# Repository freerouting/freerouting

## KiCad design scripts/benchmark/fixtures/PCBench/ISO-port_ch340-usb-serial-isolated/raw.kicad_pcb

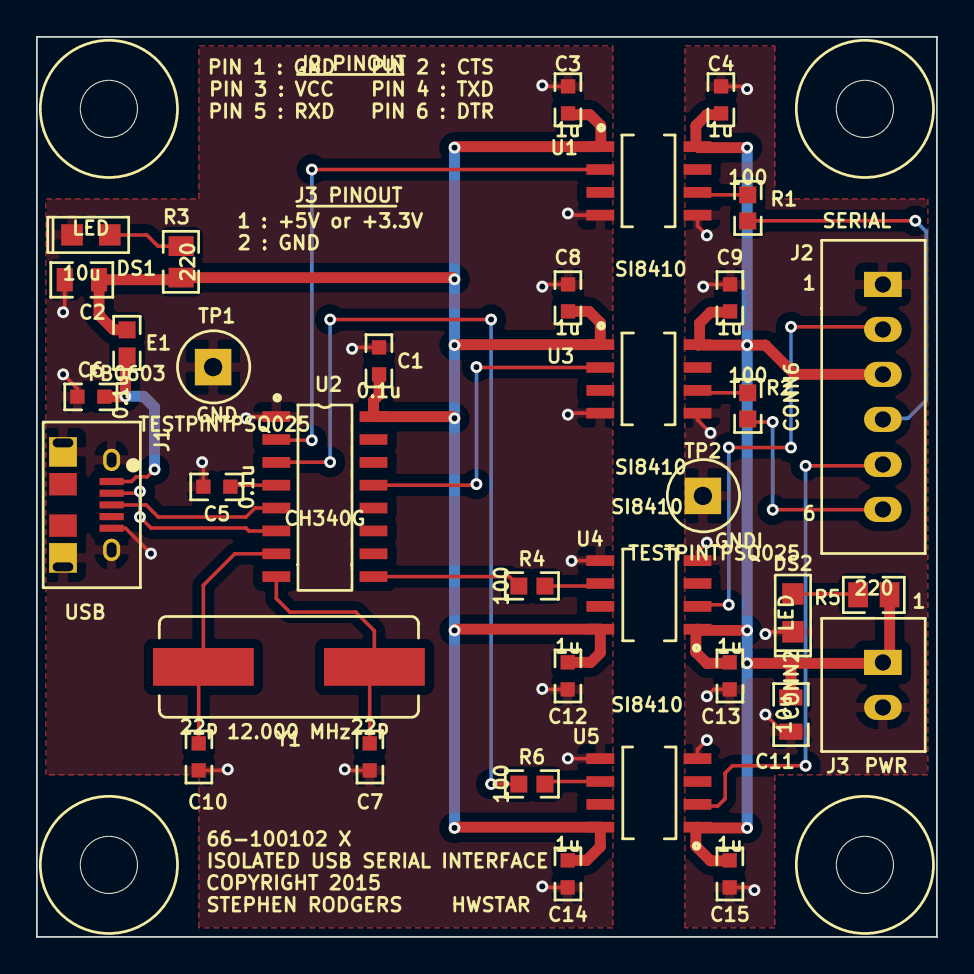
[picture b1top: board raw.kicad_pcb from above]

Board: 2 copper layers, 50.0 x 50.0 mm, 39 parts (0 on the bottom side), 24 nets.

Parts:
C1, C5, C6: 0.1u; CC0603
C2, C11: 10u; CC0805
C3, C4, C8, C9, C12, C13, C14, C15: 1u; CC0603
C7, C10: 22p; CC0603
DS1, DS2: LED; LED0805
E1: FB0603; RC0603
J1: CONN-USB-B-MICRO-FCI-11018194
J2: CONN6; JST_B6B_XH_A
J3: CONN2; JST_B2B_XH_A
MTG-HOLE-125-RING-300, MTG-HOLE-125-RING-300#2, MTG-HOLE-125-RING-300#3, MTG-HOLE-125-RING-300#4: VAL**; MTG-HOLE-125-RING-300
R1, R2, R4, R6: 100; RC0603
R3, R5: 220; RC0805
TP1, TP2: TESTPINTPSQ025; TESTPIN
U1, U3, U4, U5: SI8410; SOIC8N-SI8410
U2: CH340G; SOIC16N-SAR
Y1: 12.000 MHz; HC49US-SAR

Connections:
+5V: C1.1, C2.1, C3.1, C8.1, C12.1, C14.1, E1.2, R3.1, U1.1, U2.16, U3.1, U4.8, U5.8
+5VI: C4.1, C9.1, C11.1, C13.1, C15.1, J2.3, J3.1, R5.1, U1.8, U3.8, U4.1, U5.1
/CTSI: J2.2, U4.2
/CTSU: R4.1, U2.9
/D+: J1.3, U2.5
/D-: J1.2, U2.6
/DTRI: J2.6, R2.2
/DTRU: U2.13, U3.2
/RXDI: J2.5, U5.2
/RXDU: R6.1, U2.3
/TXDI: J2.4, R1.2
/TXDU: U1.2, U2.2
/VBUS: C6.1, E1.1, J1.1
GND: C1.2, C2.2, C3.2, C5.2, C6.2, C7.2, C8.2, C10.2, C12.2, C14.2, DS1.2, J1.5, J1.6, J1.7, J1.8, J1.9, TP1.1, U1.4, U2.1, U3.4, U4.5, U5.5
GNDI: C4.2, C9.2, C11.2, C13.2, C15.2, DS2.2, J2.1, J3.2, TP2.1, U1.5, U3.5, U4.4, U5.4
unnamed: R1.1, U1.6
unnamed: R6.2, U5.6
unnamed: DS2.1, R5.2
unnamed: DS1.1, R3.2
unnamed: R2.1, U3.6
unnamed: R4.2, U4.6
unnamed: C10.1, U2.7, Y1.1
unnamed: C5.1, U2.4
unnamed: C7.1, U2.8, Y1.2

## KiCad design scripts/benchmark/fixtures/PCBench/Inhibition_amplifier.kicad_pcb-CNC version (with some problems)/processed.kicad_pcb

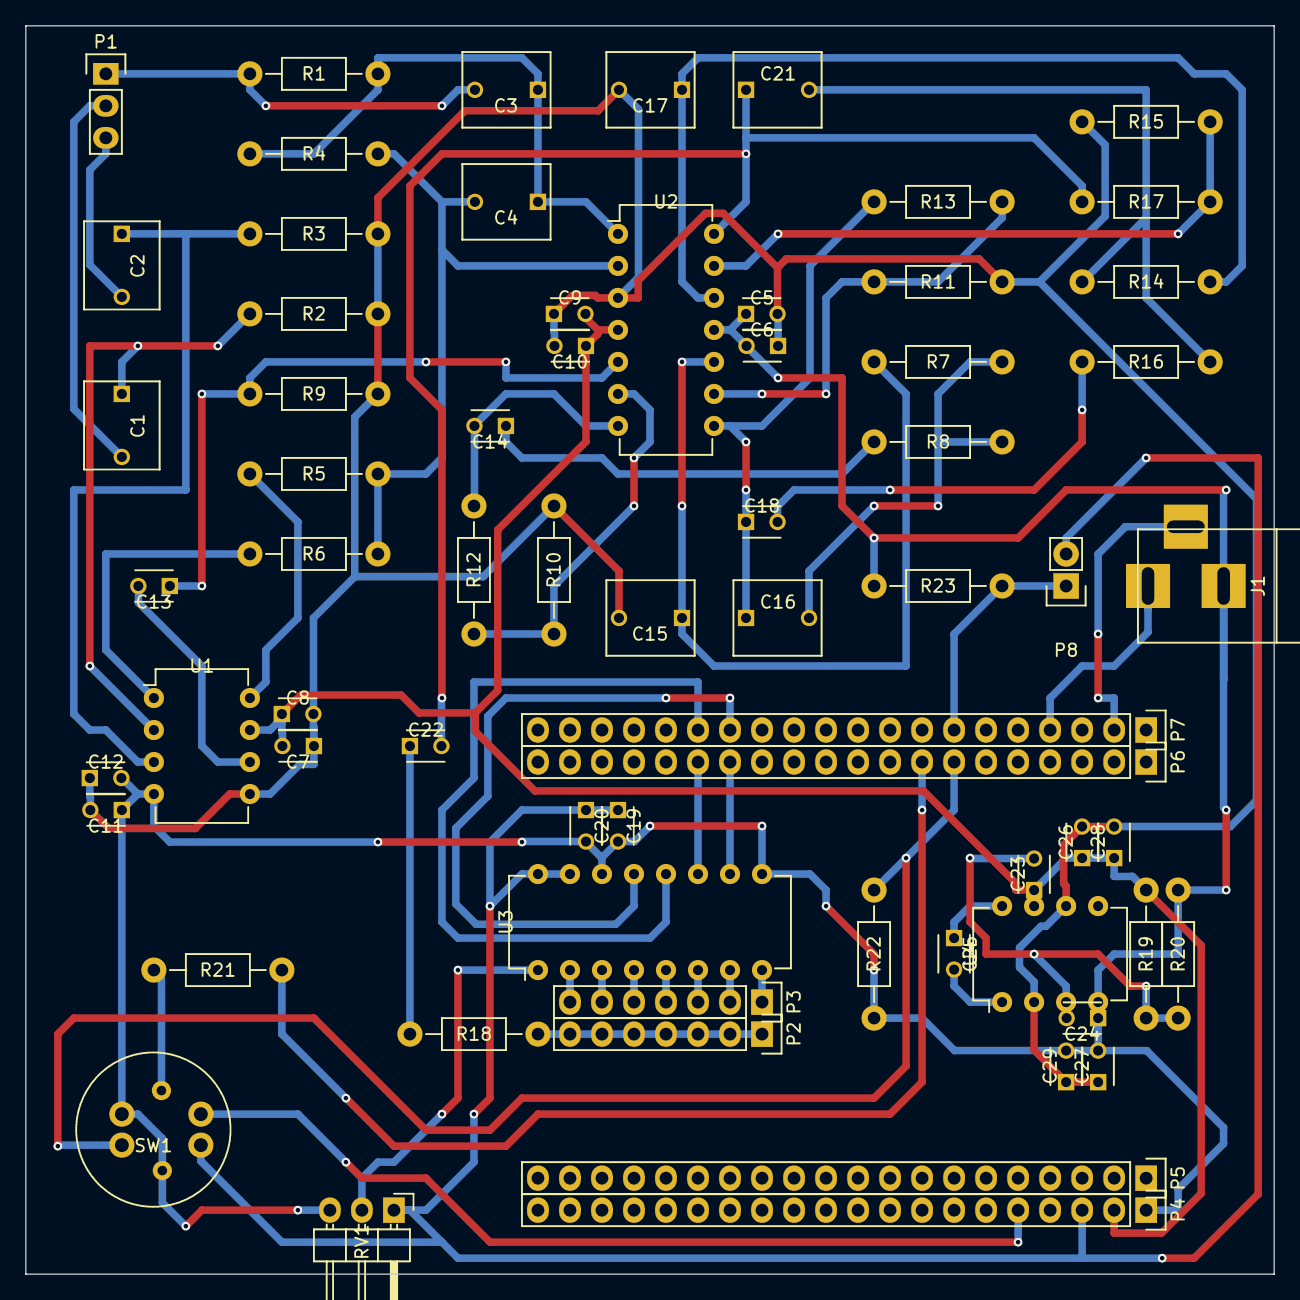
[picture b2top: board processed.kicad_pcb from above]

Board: 2 copper layers, 99.1 x 99.1 mm, 67 parts (0 on the bottom side), 51 nets.

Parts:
C1, C2: 0.01μ; C_Rect_L7_W6_P5
C3, C4: 1n; C_Rect_L7_W6_P5
C5, C7, C9, C11, C19: 0.01μ; C_Disc_D3_P2.5
C6, C8, C10, C12, C20: 0.33μ; C_Disc_D3_P2.5
C13, C14, C18, C22, C28, C29: 10μ; C_Disc_D3_P2.5
C15, C17: 0.47μ; C_Rect_L7_W6_P5
C16, C21: 0.82μ; C_Rect_L7_W6_P5
C23, C24: .01μ; C_Disc_D3_P2.5
C25: 1n; C_Disc_D3_P2.5
C26, C27: 1μ; C_Disc_D3_P2.5
J1: JACK_2P; BARREL_JACK
P1: CONN_01X03; Pin_Header_Straight_1x03
P2, P3: CONN_01X07; Pin_Header_Straight_1x07
P4, P5, P6, P7: CONN_01X20; Pin_Header_Straight_1x20
P8: CONN_01X02; Pin_Header_Straight_1x02
R1, R4: 100K; Resistor_Horizontal_RM10mm
R2, R3: 15M; Resistor_Horizontal_RM10mm
R5, R6: 100; Resistor_Horizontal_RM10mm
R7, R8, R9, R10, R11, R14, R15, R16, R19, R22, R23: 10K; Resistor_Horizontal_RM10mm
R12, R13, R17: 470K; Resistor_Horizontal_RM10mm
R18: 220; Resistor_Horizontal_RM10mm
R20: 15K; Resistor_Horizontal_RM10mm
R21: 1K; Resistor_Horizontal_RM10mm
RV1: POT; Pin_Header_Angled_1x03
SW1: Switch_DPST; Switch_LED
U1: AD620; DIP-8_W7.62mm
U2: LM324; DIP-14_W7.62mm
U3: MCP3008; DIP-16_W7.62mm
U4: CA3140; DIP-8_W7.62mm

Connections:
GND: C5.2, C6.1, C7.1, C8.2, C9.1, C10.2, C11.2, C12.1, C15.2, C17.2, C26.2, C27.1, C28.2, C29.1, R2.2, R3.2, R9.2, R10.2, R11.2, R15.2, U1.5, U2.3, U4.2, U4.6
unnamed: C1.1, R2.1, U1.2
unnamed: C1.2, P1.2
unnamed: C2.1, R3.1, U1.3
unnamed: C2.2, P1.3
unnamed: C3.1, C4.1, R1.1, R4.1, U2.1
unnamed: C3.2, P1.1, R1.2
unnamed: C4.2, R4.2, R5.2, R6.1, U2.2
unnamed: C13.1, R9.1, U2.5
unnamed: C13.2, U1.6
unnamed: C14.1, R8.2
unnamed: C14.2, R12.1, U2.7
unnamed: C15.1, R7.1, U2.10
unnamed: C16.1, C18.1, R13.1, U2.8
unnamed: C16.2, R7.2, R8.1
unnamed: C17.1, R14.2, U2.12
unnamed: C18.2, R16.2
unnamed: C19.1, C20.1, P4.3, P8.2, RV1.1, SW1.4, U3.15, U3.16
unnamed: C21.1, C22.2, R17.1, U2.14
unnamed: C21.2, R14.1, R16.1
unnamed: C22.1, R18.1
unnamed: C23.2, C24.2, R19.2, R20.1, U4.3
unnamed: C25.1, U4.8
unnamed: C25.2, U4.1
unnamed: J1.1, P7.4
unnamed: J1.3, P7.2
unnamed: P2.1, P2.2, P2.3, P2.4, P2.5, P2.6, P2.7, R18.2
unnamed: P3.1, U3.8
unnamed: P3.2, U3.7
unnamed: P3.3, U3.6
unnamed: P3.4, U3.5
unnamed: P3.5, U3.4
unnamed: P3.6, U3.3
unnamed: P3.7, U3.2
unnamed: P4.5, SW1.2
unnamed: P6.7, R22.1, SW1.3
unnamed: P6.8, R21.2
unnamed: P6.14, U3.10
unnamed: P6.15, U3.11
unnamed: P7.7, P8.1, R23.1
unnamed: P7.14, U3.13
unnamed: P7.15, U3.12
unnamed: R5.1, U1.8
unnamed: R6.2, U1.1
unnamed: R10.1, R12.2, U2.6
unnamed: R11.1, R13.2, U2.9
unnamed: R15.1, R17.2, U2.13
unnamed: R21.1, SW1.5
unnamed: RV1.2, U3.1
VCC: C7.2, C8.1, C9.2, C10.1, C23.1, C26.1, C28.1, P4.2, R19.1, U1.7, U2.4, U4.7
VEE: C5.1, C6.2, C11.1, C12.2, C19.2, C20.2, C24.1, C27.2, C29.2, J1.2, P4.1, R20.2, R22.2, R23.2, RV1.3, SW1.1, SW1.6, U1.4, U2.11, U3.9, U3.14, U4.4

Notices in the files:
scripts/benchmark/fixtures/PCBench/ISO-port_ch340-usb-serial-isolated/raw.kicad_pcb:
COPYRIGHT 2015
